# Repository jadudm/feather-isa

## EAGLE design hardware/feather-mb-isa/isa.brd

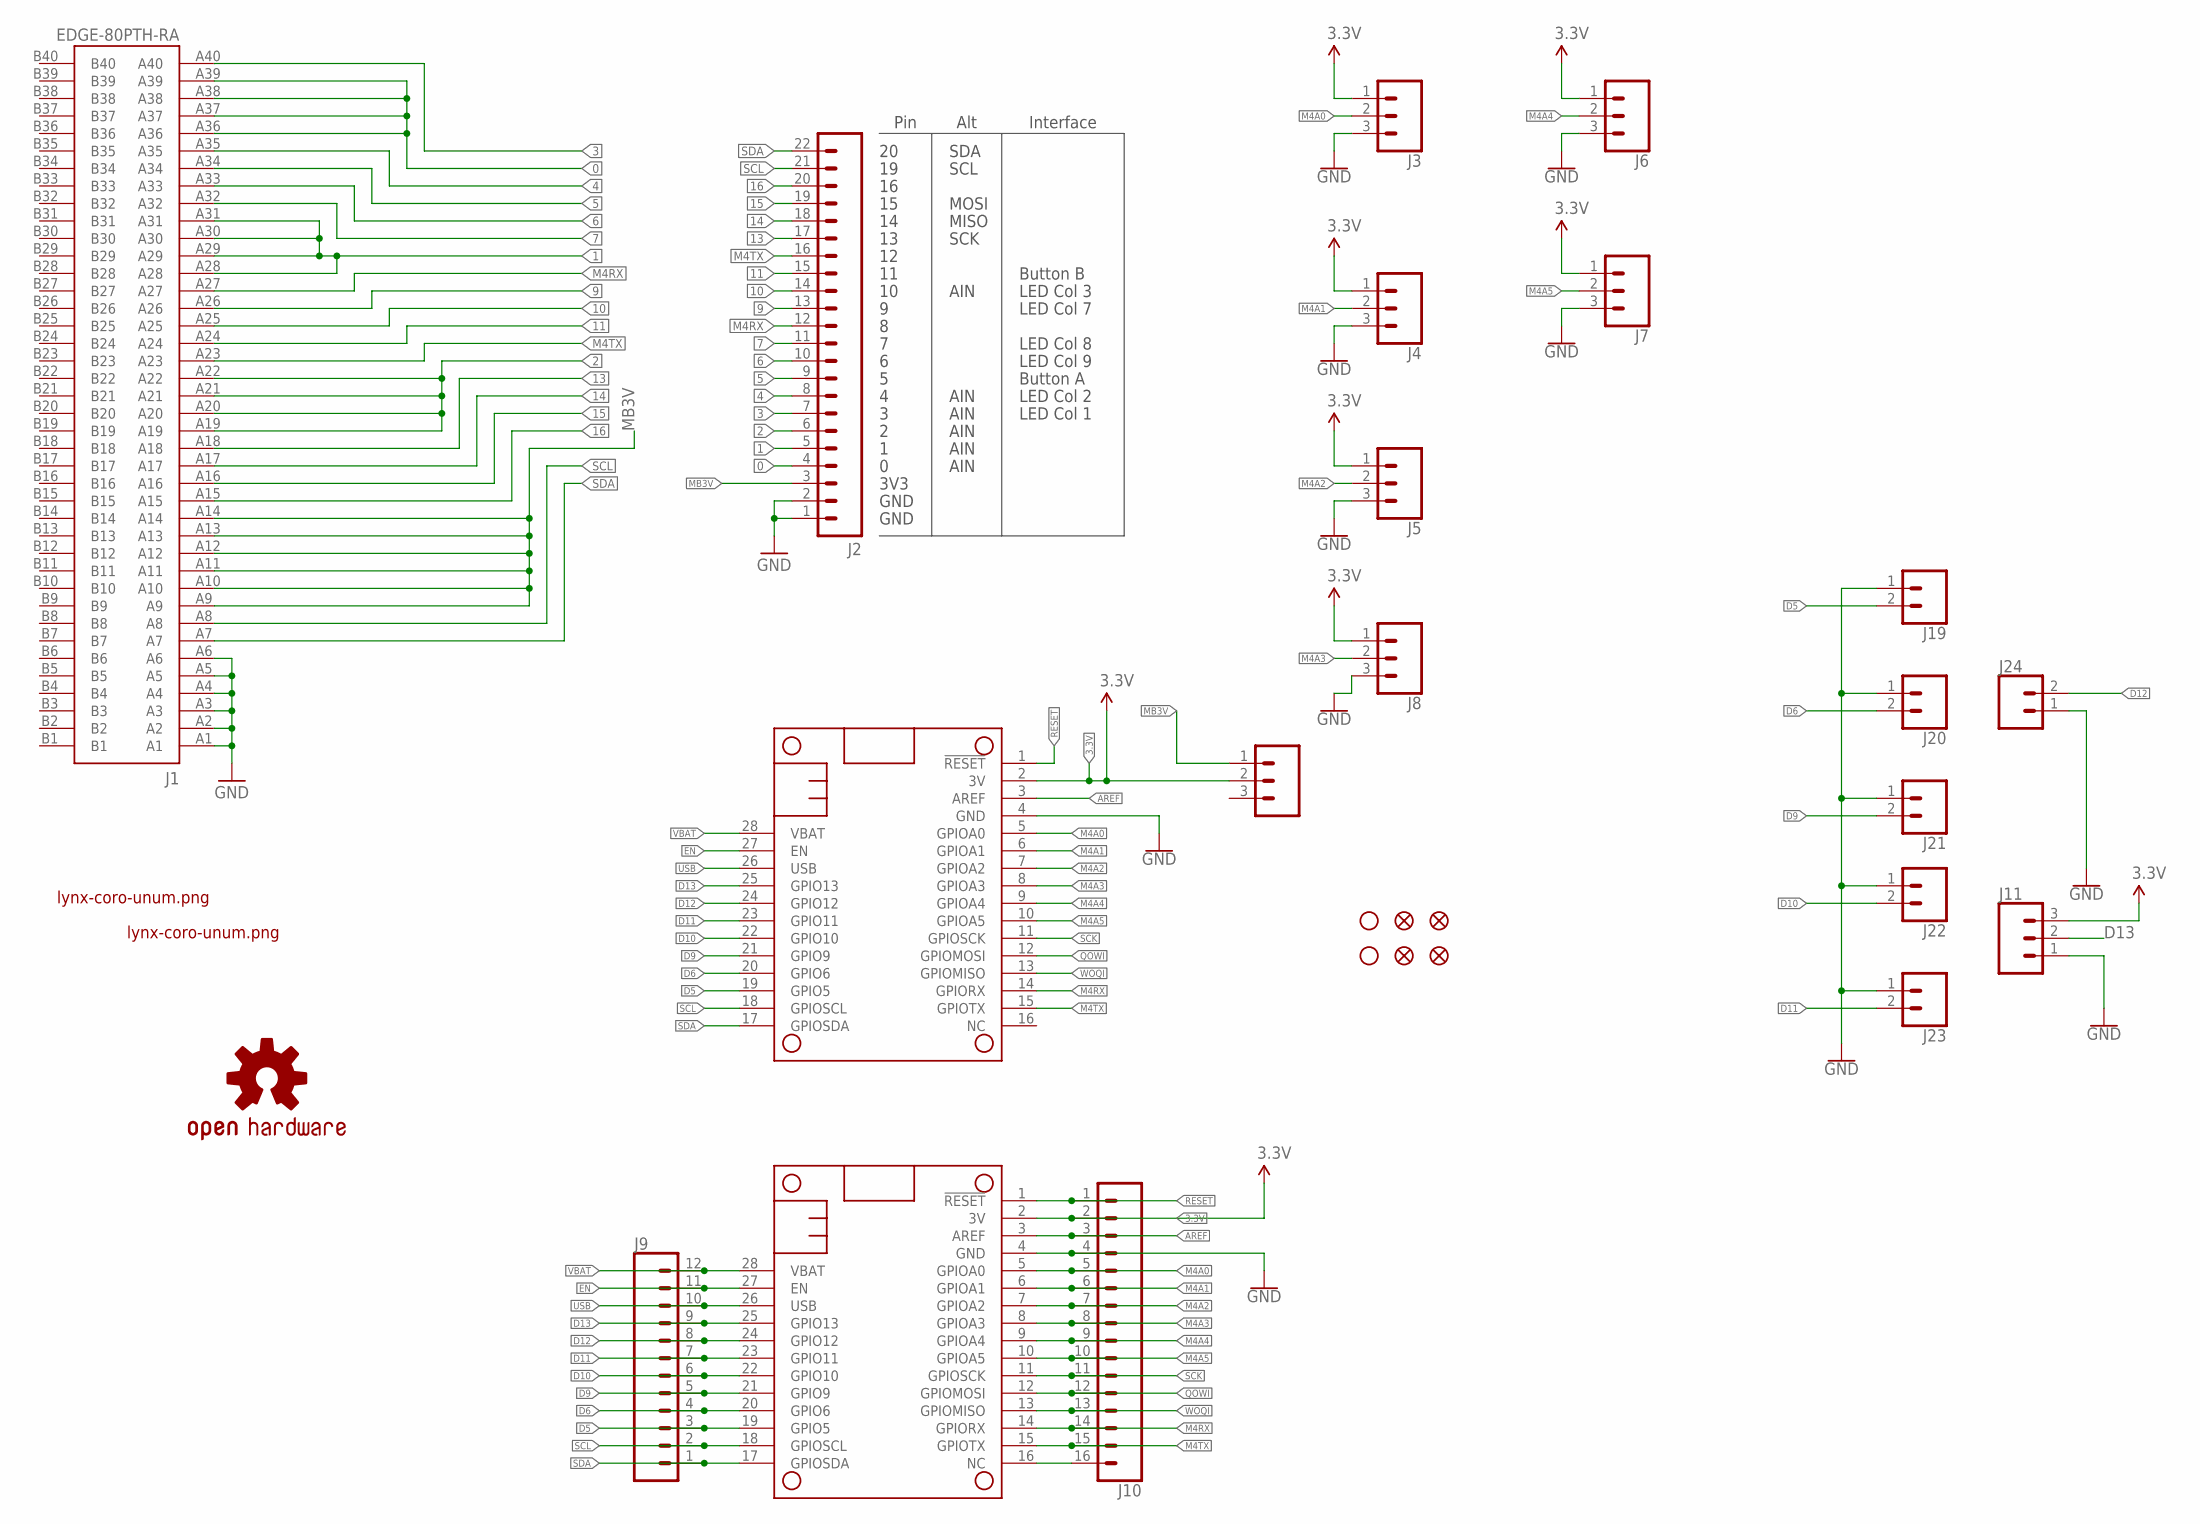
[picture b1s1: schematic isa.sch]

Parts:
FD1, FD2, FD3, FD4: FIDUCIAL1X2; FIDUCIAL-1X2
H1, H2: STAND-OFF
J1: EDGE-80PTH-RA; VEC-127-080-R
J2: M22PTH; 1X22
J3, J4, J5, J6, J7, J8, J11: CONN_03SCREW; SCREWTERMINAL-3.5MM-3
J9: CONN_12LOCK; 1X12_LOCK
J10: CONN_16LOCK; 1X16_LOCK
J12: CONN_03; 1X03
J19, J20, J21, J22, J23, J24: CONN_023.5MM; SCREWTERMINAL-3.5MM-2
LOGO3: OSHW-LOGOS; OSHW-LOGO-S
MS1, MS2: FEATHERWING_NODIM; FEATHERWING_DIM
U$3, U$4: LYNX#CORO#UNUM#PNG

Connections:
0: J1.A36, J1.A37, J1.A38, J1.A39, J2.4
1: J1.A28, J1.A29, J1.A30, J1.A31, J2.5
2: J1.A19, J1.A20, J1.A21, J1.A22, J2.6
3: J1.A40, J2.7
3.3V: J3.1, J4.1, J5.1, J6.1, J7.1, J8.1, J10.2, J11.3, J12.2, MS1.2 (3V), MS2.2 (3V)
4: J1.A35, J2.8
5: J1.A34, J2.9
6: J1.A33, J2.10
7: J1.A32, J2.11
9: J1.A26, J2.13
10: J1.A25, J2.14
11: J1.A24, J2.15
13: J1.A18, J2.17
14: J1.A17, J2.18
15: J1.A16, J2.19
16: J1.A15, J2.20
AREF: J10.3, MS1.3 (AREF), MS2.3 (AREF)
D5: J9.3, J19.2, MS1.19 (GPIO5), MS2.19 (GPIO5)
D6: J9.4, J20.2, MS1.20 (GPIO6), MS2.20 (GPIO6)
D9: J9.5, J21.2, MS1.21 (GPIO9), MS2.21 (GPIO9)
D10: J9.6, J22.2, MS1.22 (GPIO10), MS2.22 (GPIO10)
D11: J9.7, J23.2, MS1.23 (GPIO11), MS2.23 (GPIO11)
D12: J9.8, J24.2, MS1.24 (GPIO12), MS2.24 (GPIO12)
D13: J9.9, J11.2, MS1.25 (GPIO13), MS2.25 (GPIO13)
EN: J9.11, MS1.27 (EN), MS2.27 (EN)
GND: J1.A1, J1.A2, J1.A3, J1.A4, J1.A5, J1.A6, J2.1, J2.2, J3.3, J4.3, J5.3, J6.3, J7.3, J8.3, J10.4, J11.1, J19.1, J20.1, J21.1, J22.1, J23.1, J24.1, MS1.4 (GND), MS2.4 (GND)
M4A0: J3.2, J10.5, MS1.5 (GPIOA0), MS2.5 (GPIOA0)
M4A1: J4.2, J10.6, MS1.6 (GPIOA1), MS2.6 (GPIOA1)
M4A2: J5.2, J10.7, MS1.7 (GPIOA2), MS2.7 (GPIOA2)
M4A3: J8.2, J10.8, MS1.8 (GPIOA3), MS2.8 (GPIOA3)
M4A4: J6.2, J10.9, MS1.9 (GPIOA4), MS2.9 (GPIOA4)
M4A5: J7.2, J10.10, MS1.10 (GPIOA5), MS2.10 (GPIOA5)
M4RX: J1.A27, J2.12, J10.14, MS1.14 (GPIORX), MS2.14 (GPIORX)
M4TX: J1.A23, J2.16, J10.15, MS1.15 (GPIOTX), MS2.15 (GPIOTX)
MB3V: J1.A9, J1.A10, J1.A11, J1.A12, J1.A13, J1.A14, J2.3, J12.1
unnamed: J10.16, MS2.16 (NC)
QOWI: J10.12, MS1.12 (GPIOMOSI), MS2.12 (GPIOMOSI)
RESET: J10.1, MS1.1 (!RESET), MS2.1 (!RESET)
SCK: J10.11, MS1.11 (GPIOSCK), MS2.11 (GPIOSCK)
SCL: J1.A8, J2.21, J9.2, MS1.18 (GPIOSCL), MS2.18 (GPIOSCL)
SDA: J1.A7, J2.22, J9.1, MS1.17 (GPIOSDA), MS2.17 (GPIOSDA)
USB: J9.10, MS1.26 (USB), MS2.26 (USB)
VBAT: J9.12, MS1.28 (VBAT), MS2.28 (VBAT)
WOQI: J10.13, MS1.13 (GPIOMISO), MS2.13 (GPIOMISO)

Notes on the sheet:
GND
3V3
SCL
SDA
SCK
MISO
MOSI
AIN
Button B
LED Col 3
LED Col 7
LED Col 8
LED Col 9
LED Col 2
Button A
LED Col 1
Pin
Alt
Interface

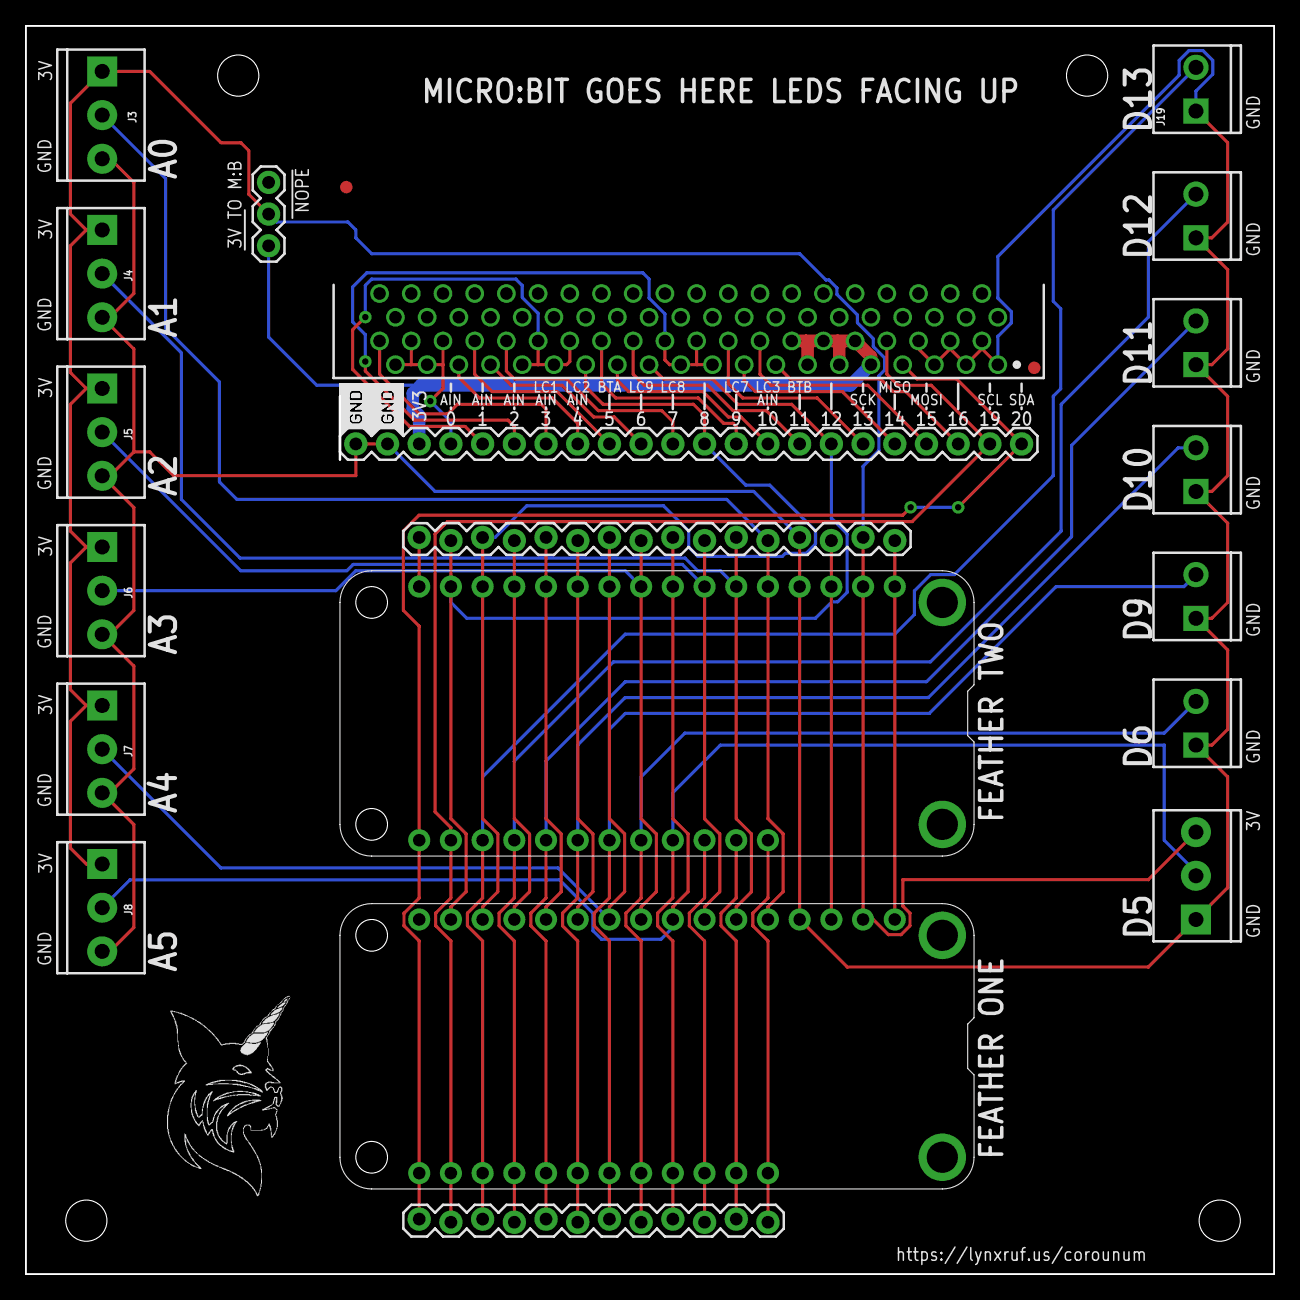
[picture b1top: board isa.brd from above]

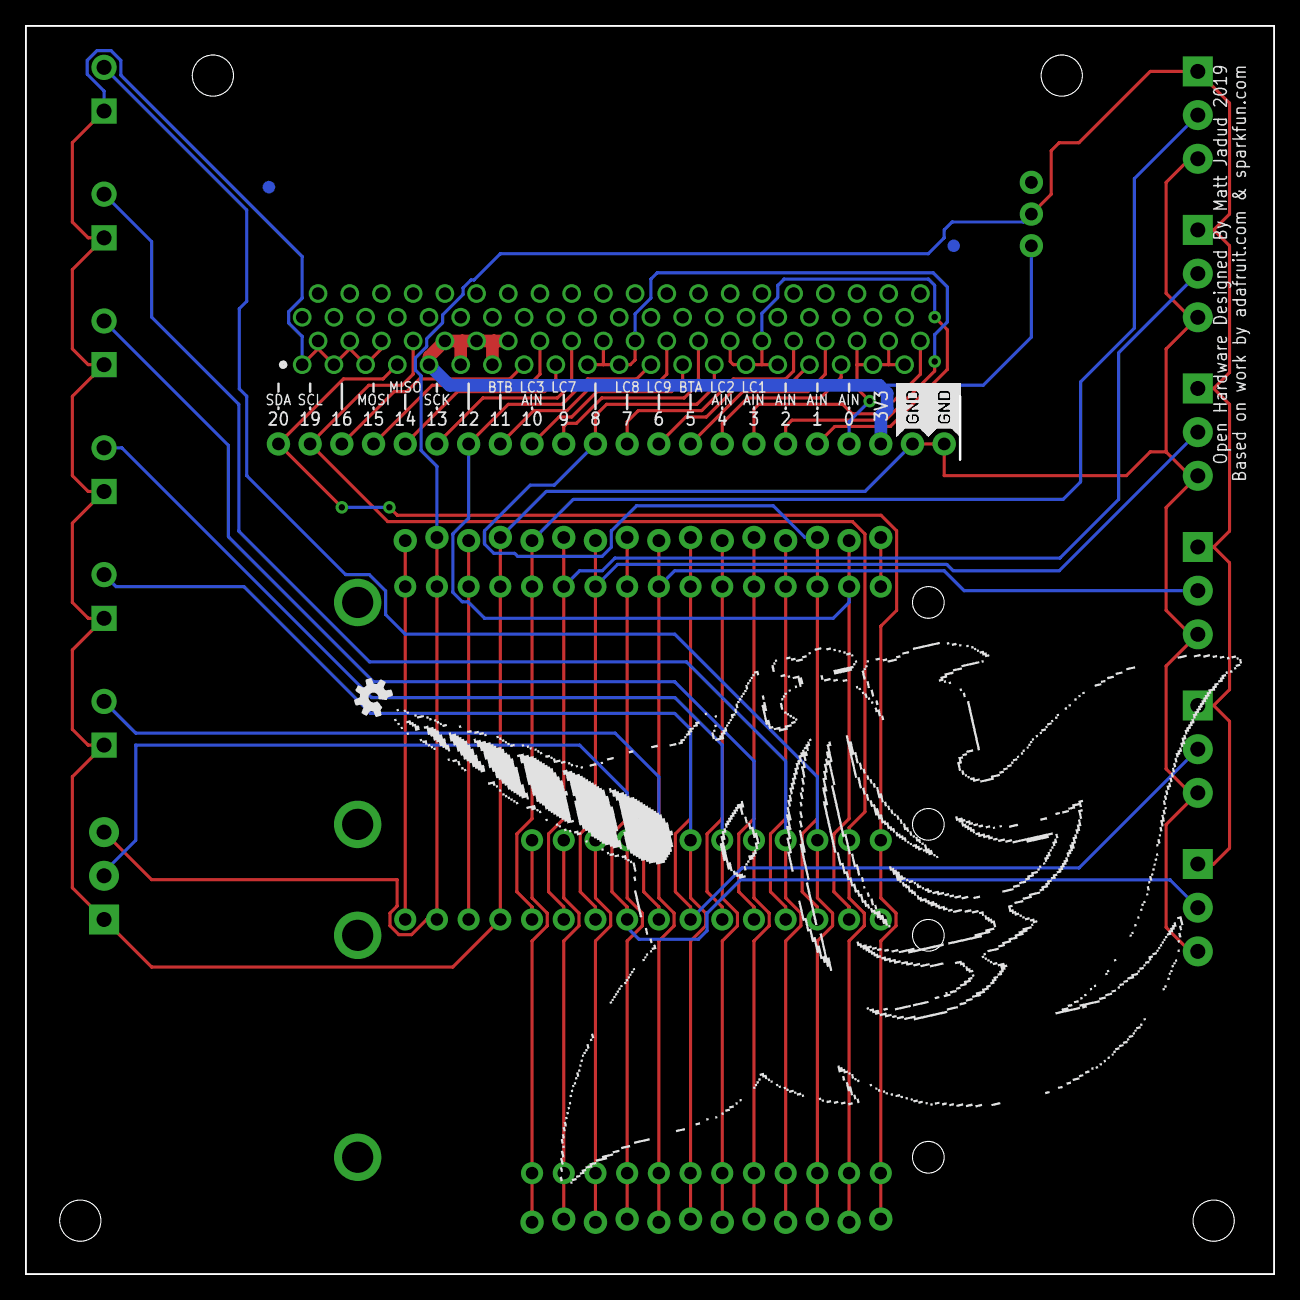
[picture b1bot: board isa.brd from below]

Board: 2 copper layers, 99.9 x 99.9 mm, 33 parts (5 on the bottom side), 44 nets.

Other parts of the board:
H3, H4: STAND-OFF
U$1, U$2: NEGASILK_MICRO_BIT_BREAKOUT

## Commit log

2019-05-13 First commit.
2019-05-13 Adding in an LED twiddle.
2019-05-13 Added a timeout.
    This was necessary. The UART will get stuck mid-message if I'm not careful.
2019-05-13 Adding a URL.
2019-05-13 Working on MIDI
    About to try and speed it up. Saving this version.
    :
2019-05-13 Faster?
    Not really.
    We hit a limit for neopixel update at around 50ms. It seems awfully slow.
2019-05-13 Adding in lots of things.
2019-05-13 Added the ability to flush all.
2019-05-14 Renamed midi.py
    Now can be main.
    Updated hardware. Looks ready for layout. Need to do some more
    work in the middle. What to do with that space? Some neopixels?
    Some buttons?
    More headers?
2019-05-14 Changes.
2019-05-14 Updates to the board.
    It would be good to have one pin with power. The ids are all out of order on the RH side.
2019-05-15 Moving things around.
2019-05-16 About to change Python... `:
2019-05-16 Moving towards a new Neopixel interface.
    Sending four vals at once.
2019-05-17 Now setting ranges of pixels.
2019-05-17 Added license.
2019-05-17 Trying to fix our broken protocol.
    MUST. REDESIGN.
2019-05-18 Removing old libs.
2019-05-18 Exploring C++
    I want performance. Perhaps this should be written in C.
2019-05-18 Starting on PIO. Was easy to set up, lets me work in another editor.
2019-05-18 Adding patch.
2019-05-18 MIDI parsing, improved.
    Better than state machine, I hope. I'm not sure what Max is doing,
    but I seem to need to slurp several messages at once.
2019-05-18 Updating ignore for vscode.
2019-05-18 Reading/comms look good.
    That took a long time. I'm still not happy about some things, but ...
    Blasting data from Max, reading it in C++. The packet reading state machine seems reasonable. It seems to break under too heavy a load. I have to check that there are enough ->START transitions.
2019-05-18 Working well.
    I'm now driving the Neopixel ring at 5ms on update, and the ring flies.
    No protocol issues. So far.
2019-05-19 Digital buttons working.
    The analog pins get really noisy when you start driving a Neopixel ring.
2019-05-19 Reworking digital.
    Adding a 50ms check timer. Buttons now happen... 20x a second.
    That should be fast enough.
    `
2019-05-19 Serial and MIDI
    I really need to do more unification. However, both packet formats
    now align.
2019-05-20 Serial and midi working. `
2019-05-20 Things remain working.
    I need a better way to debug the feather. A real JTAG with the Grand Central would be nice.
    I've pasted in the Typescript for the new Micro:Bit extension.
    I don't want to update that until the show is over, as it will screw
    the students in their work.
    Done for the night.
2019-05-20 Playing with the patch.
    Need to parse UARTs better.
2019-05-21 Fixes... should port back to main.
2019-05-22 For exploring a GOTO based state machine.
2019-05-24 Compiling version of firmware.
    This is broken apart into separate files, for better separation of concerns and just plain sanity.
2019-06-11 Failed to commit...

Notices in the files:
parts and their libraries:
SparkFun-Aesthetics: Licensing: Creative Commons ShareAlike 4.0 International - https://creativecommons.org/licenses/by-sa/4.0
